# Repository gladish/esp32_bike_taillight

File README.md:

# bikelight
ESP32 Bike Rear Light

<table>
  <tr>
    <td><br>Front</td>
    <td><br>Side</td>
    <td><br>Back</td>
  </tr>
</table>

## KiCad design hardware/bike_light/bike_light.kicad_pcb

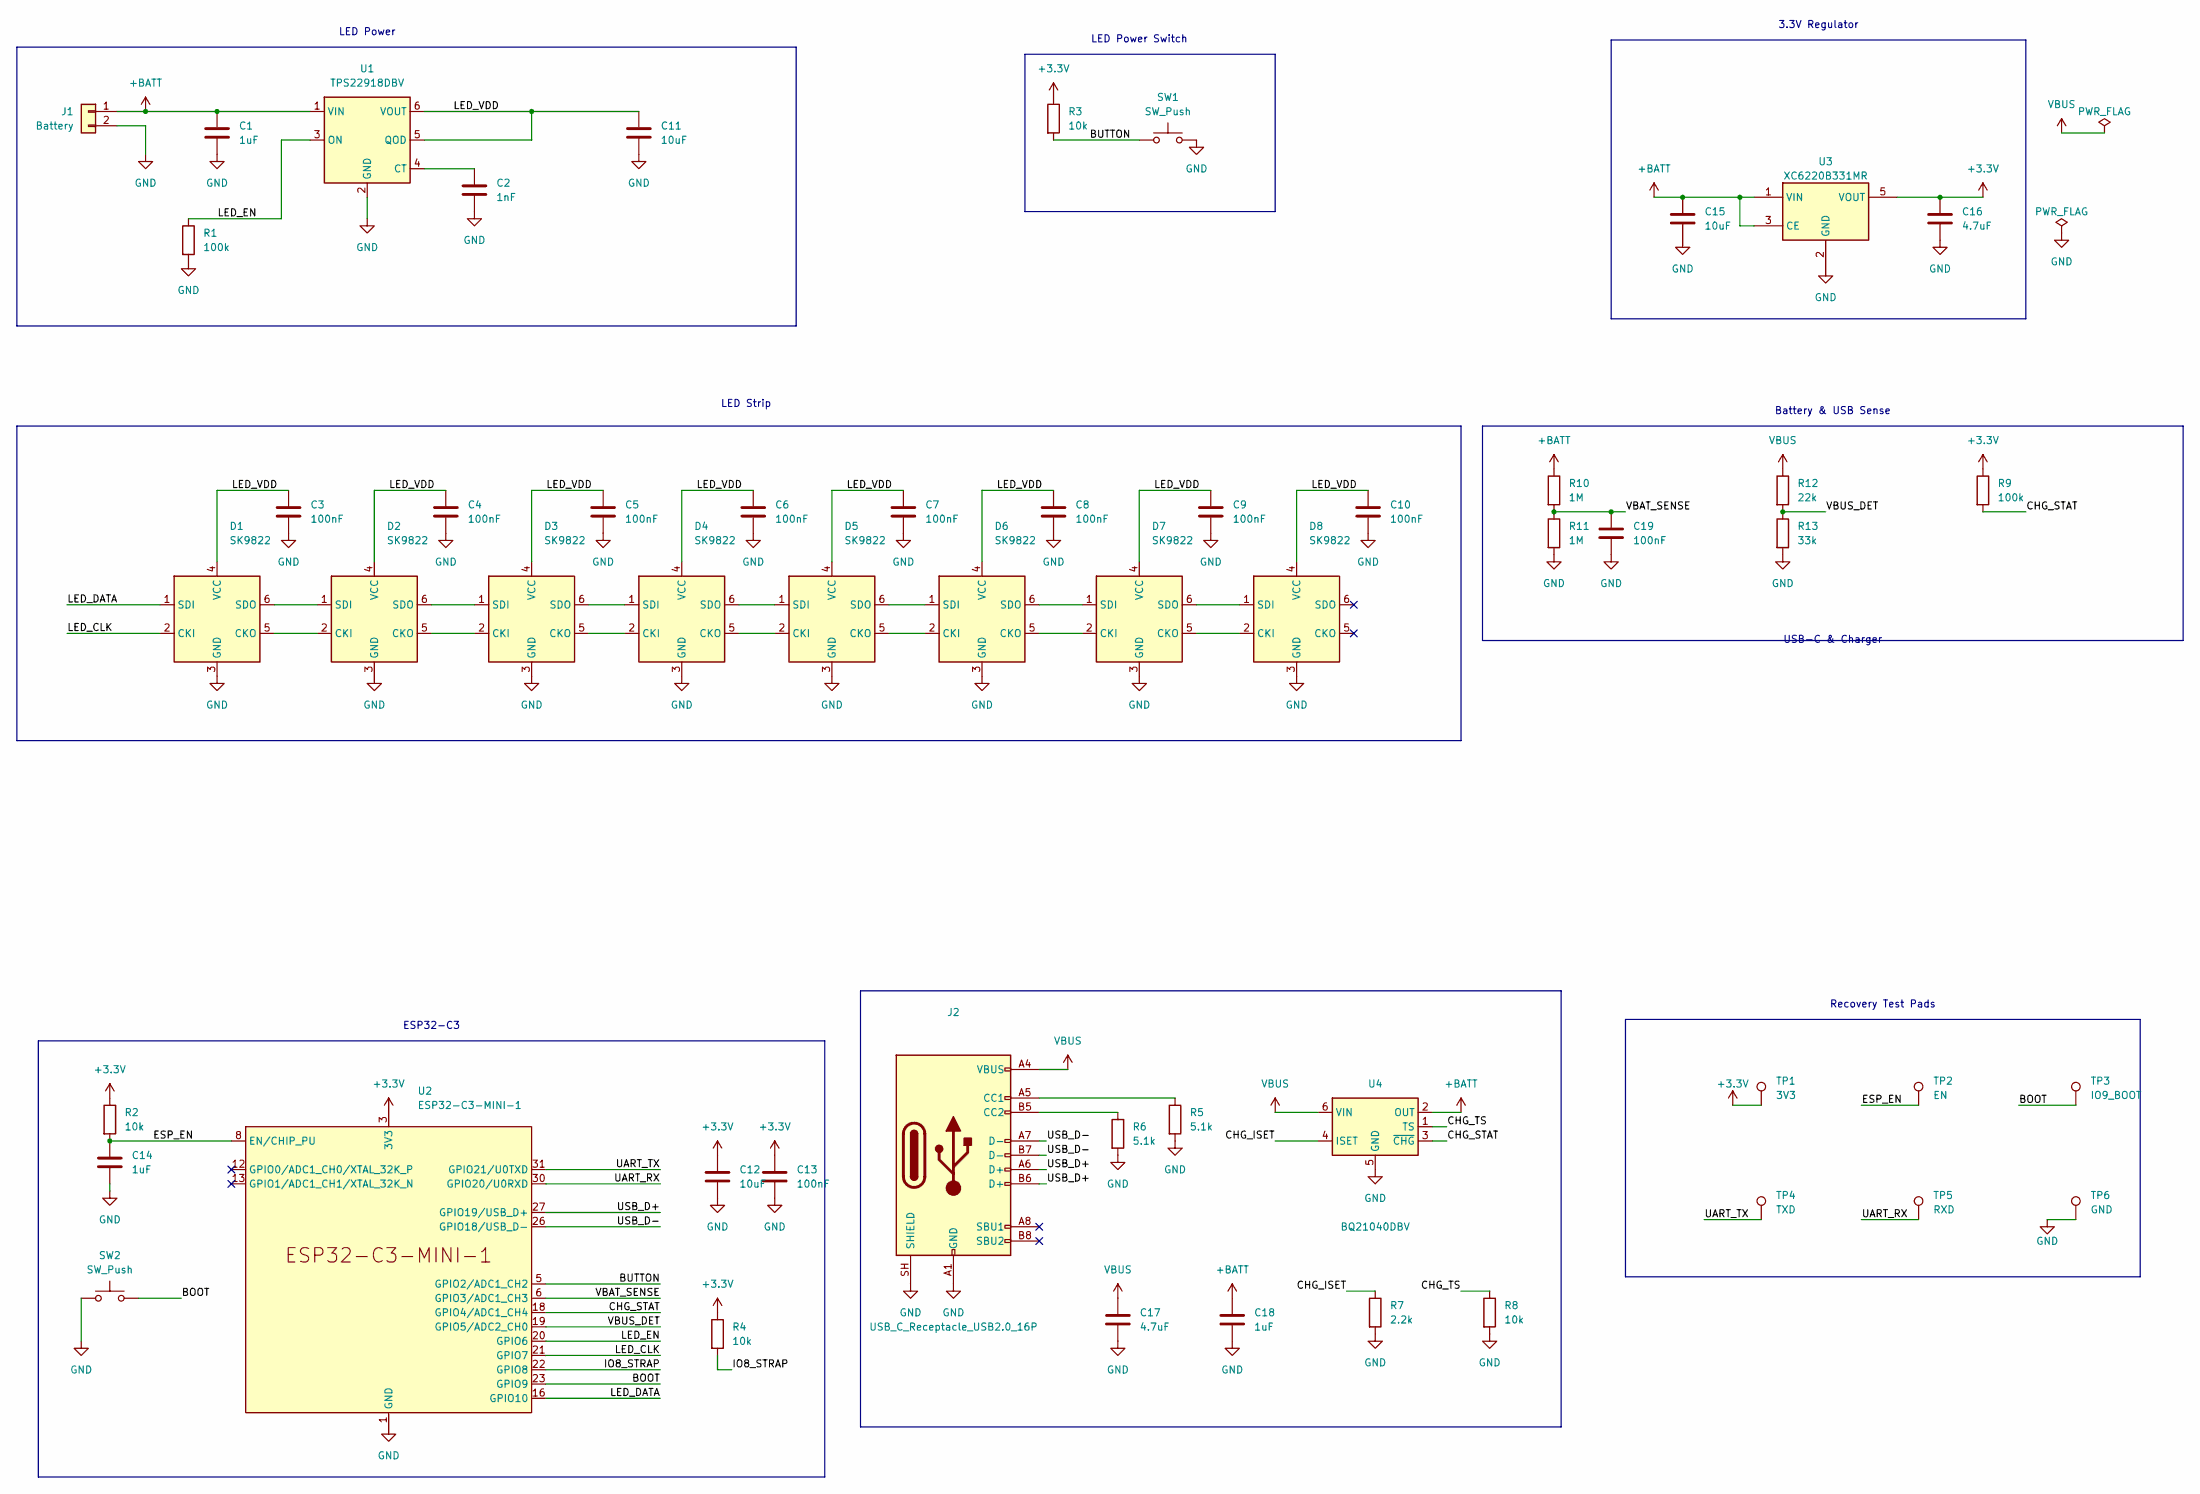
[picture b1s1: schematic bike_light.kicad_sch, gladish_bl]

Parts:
C1, C14, C18: 1uF; C_0402_1005Metric
C2: 1nF; C_0402_1005Metric
C3, C4, C5, C6, C7, C8, C9, C10, C13, C19: 100nF; C_0402_1005Metric
C11, C12, C15: 10uF; C_0603_1608Metric
C16, C17: 4.7uF; C_0603_1608Metric
D1, D2, D3, D4, D5, D6, D7, D8: SK9822; LED_RGB_5050-6
J1: Battery; JST_SH_SM02B-SRSS-TB_1x02-1MP_P1.00mm_Horizontal
J2: USB_C_Receptacle_USB2.0_16P; USB_C_Receptacle_HRO_TYPE-C-31-M-12
R1, R9: 100k; R_0402_1005Metric
R2, R3, R4, R8: 10k; R_0402_1005Metric
R5, R6: 5.1k; R_0402_1005Metric
R7: 2.2k; R_0402_1005Metric
R10, R11: 1M; R_0402_1005Metric
R12: 22k; R_0402_1005Metric
R13: 33k; R_0402_1005Metric
SW1: SW_Push; SW_Push_1P1T-MP_NO_Horizontal_Alps_SKRTLAE010
SW2: SW_Push; SW_SPST_B3U-1000P
TP1: 3V3; TestPoint_Pad_D1.0mm
TP2: EN; TestPoint_Pad_D1.0mm
TP3: IO9_BOOT; TestPoint_Pad_D1.0mm
TP4: TXD; TestPoint_Pad_D1.0mm
TP5: RXD; TestPoint_Pad_D1.0mm
TP6: GND; TestPoint_Pad_D1.0mm
U1: TPS22918DBV; SOT-23-6
U2: ESP32-C3-MINI-1
U3: XC6220B331MR; SOT-23-5
U4: BQ21040DBV; SOT-23-6

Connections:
+3.3V: C12.1, C13.1, C16.1, R2.1, R3.1, R4.1, R9.1, TP1.1 (1_1), U2.3 (3V3), U3.5 (VOUT)
+BATT: C1.1, C15.1, C18.1, J1.1, R10.1, U1.1 (VIN), U3.1 (VIN), U3.3 (CE), U4.2 (OUT)
/BOOT: SW2.2, TP3.1 (1_1), U2.23 (GPIO9)
/BUTTON: R3.2, SW1.1, U2.5 (GPIO2/ADC1_CH2)
/CHG_ISET: R7.1, U4.4 (ISET)
/CHG_STAT: R9.2, U2.18 (GPIO4/ADC1_CH4), U4.3 (~CHG)
/CHG_TS: R8.1, U4.1 (TS)
/ESP_EN: C14.1, R2.2, TP2.1 (1_1), U2.8 (EN/CHIP_PU)
/IO8_STRAP: R4.2, U2.22 (GPIO8)
/LED_CLK: D1.2 (CKI), U2.21 (GPIO7)
/LED_DATA: D1.1 (SDI), U2.16 (GPIO10)
/LED_EN: R1.1, U1.3 (ON), U2.20 (GPIO6)
/LED_VDD: C3.1, C4.1, C5.1, C6.1, C7.1, C8.1, C9.1, C10.1, C11.1, D1.4 (VCC), D2.4 (VCC), D3.4 (VCC), D4.4 (VCC), D5.4 (VCC), D6.4 (VCC), D7.4 (VCC), D8.4 (VCC), U1.5 (QOD), U1.6 (VOUT)
/UART_RX: TP5.1 (1_1), U2.30 (GPIO20/U0RXD)
/UART_TX: TP4.1 (1_1), U2.31 (GPIO21/U0TXD)
/USB_D+: J2.A6 (D+), J2.B6 (D+), U2.27 (GPIO19/USB_D+)
/USB_D-: J2.A7 (D-), J2.B7 (D-), U2.26 (GPIO18/USB_D-)
/VBAT_SENSE: C19.1, R10.2, R11.1, U2.6 (GPIO3/ADC1_CH3)
/VBUS_DET: R12.2, R13.1, U2.19 (GPIO5/ADC2_CH0)
GND: C1.2, C2.2, C3.2, C4.2, C5.2, C6.2, C7.2, C8.2, C9.2, C10.2, C11.2, C12.2, C13.2, C14.2, C15.2, C16.2, C17.2, C18.2, C19.2, D1.3 (GND), D2.3 (GND), D3.3 (GND), D4.3 (GND), D5.3 (GND), D6.3 (GND), D7.3 (GND), D8.3 (GND), J1.2, J2.A1 (GND), J2.A12 (GND), J2.B1 (GND), J2.B12 (GND), J2.SH (SHIELD), R1.2, R5.2, R6.2, R7.2, R8.2, R11.2, R13.2, SW1.2, SW2.1, TP6.1 (1_1), U1.2 (GND), U2.1 (GND), U2.2 (GND), U2.11 (GND), U2.14 (GND), U2.36 (GND), U2.37 (GND), U2.38 (GND), U2.39 (GND), U2.40 (GND), U2.41 (GND), U2.42 (GND), U2.43 (GND), U2.44 (GND), U2.45 (GND), U2.46 (GND), U2.47 (GND), U2.48 (GND), U2.49 (GND), U2.50 (GND), U2.51 (GND), U2.52 (GND), U2.53 (GND), U3.2 (GND), U4.5 (GND)
unnamed: D1.5 (CKO), D2.2 (CKI)
unnamed: D1.6 (SDO), D2.1 (SDI)
unnamed: D2.5 (CKO), D3.2 (CKI)
unnamed: D2.6 (SDO), D3.1 (SDI)
unnamed: D3.5 (CKO), D4.2 (CKI)
unnamed: D3.6 (SDO), D4.1 (SDI)
unnamed: D4.5 (CKO), D5.2 (CKI)
unnamed: D4.6 (SDO), D5.1 (SDI)
unnamed: D5.5 (CKO), D6.2 (CKI)
unnamed: D5.6 (SDO), D6.1 (SDI)
unnamed: D6.5 (CKO), D7.2 (CKI)
unnamed: D6.6 (SDO), D7.1 (SDI)
unnamed: D7.5 (CKO), D8.2 (CKI)
unnamed: D7.6 (SDO), D8.1 (SDI)
unnamed: J2.A5 (CC1), R5.1
unnamed: J2.B5 (CC2), R6.1
unnamed: C2.1, U1.4 (CT)
VBUS: C17.1, J2.A4 (VBUS), J2.A9 (VBUS), J2.B4 (VBUS), J2.B9 (VBUS), R12.1, U4.6 (VIN)

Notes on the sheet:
LED Power Switch
LED Strip
3.3V Regulator
Recovery Test Pads
Battery & USB Sense
ESP32-C3
USB-C & Charger
LED Power

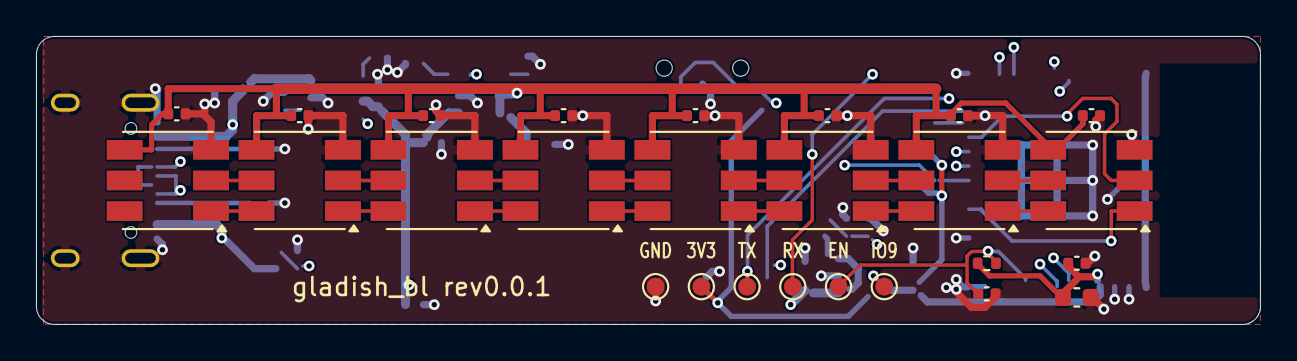
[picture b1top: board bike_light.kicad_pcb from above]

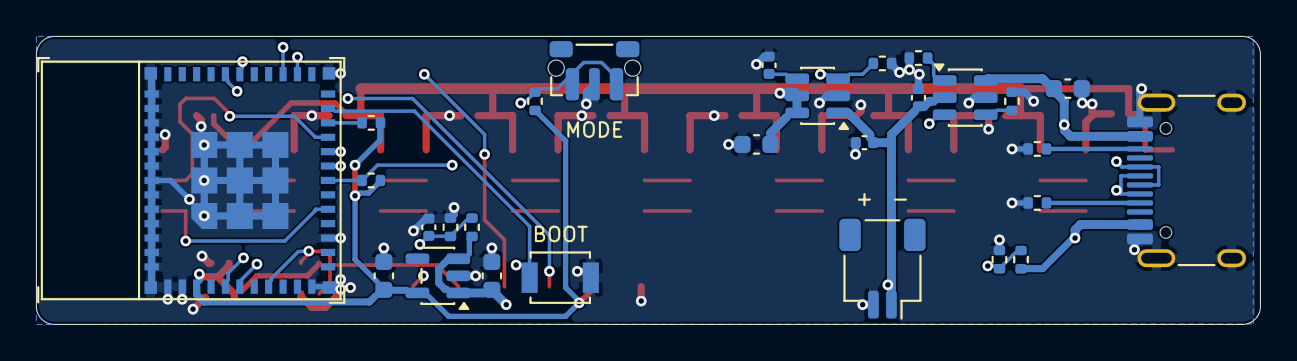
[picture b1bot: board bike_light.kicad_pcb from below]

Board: 4 copper layers, 68.0 x 16.0 mm, 54 parts (28 on the bottom side), 38 nets.

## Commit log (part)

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2026-05-17 Some cosmetic changes
2026-05-17 Original OneButton impl
2026-05-18 Added setup mode without implementation
2026-05-19 Experiementing with espressif components
2026-05-20 Replaced deprecated sleep function. Turned brightness down
2026-05-21 Added all render modes
2026-05-22 Try to prevent random LEDs turning on during charging
2026-05-22 remove unneeded header
2026-05-24 Added enum for render modes
2026-05-24 Refactored int LedPatterns
2026-05-25 Gatt server. Needs review
